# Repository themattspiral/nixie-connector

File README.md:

#nixie-connector

EAGLE schematic and board layout for my Nixie tube connector board for the ArduiNIX shield.

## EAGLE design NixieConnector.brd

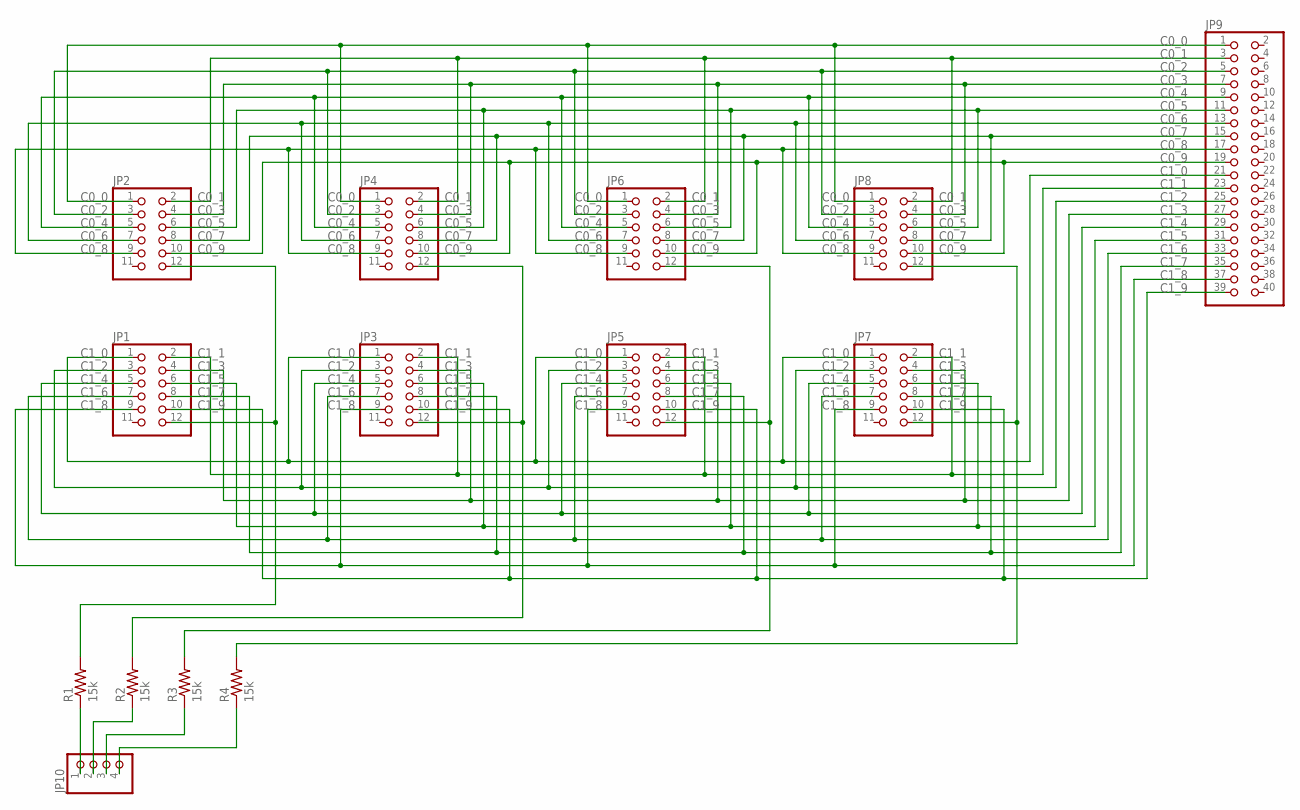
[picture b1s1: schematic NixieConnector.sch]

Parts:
JP1, JP2, JP3, JP4, JP5, JP6, JP7, JP8: PINHD-2X6; 2X06
JP9: PINHD-2X20; 2X20
JP10: PINHD-1X4; 1X04
R1, R2, R3, R4: 15k; 0204/5

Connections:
A1_IN: JP10.1, R1.1
A1_R: JP1.12, JP2.12, R1.2
A2_IN: JP10.2, R2.1
A2_R: JP3.12, JP4.12, R2.2
A3_IN: JP10.3, R3.1
A3_R: JP5.12, JP6.12, R3.2
A4_IN: JP10.4, R4.1
A4_R: JP7.12, JP8.12, R4.2
C0_0: JP2.1, JP4.1, JP6.1, JP8.1, JP9.1
C0_1: JP2.2, JP4.2, JP6.2, JP8.2, JP9.3
C0_2: JP2.3, JP4.3, JP6.3, JP8.3, JP9.5
C0_3: JP2.4, JP4.4, JP6.4, JP8.4, JP9.7
C0_4: JP2.5, JP4.5, JP6.5, JP8.5, JP9.9
C0_5: JP2.6, JP4.6, JP6.6, JP8.6, JP9.11
C0_6: JP2.7, JP4.7, JP6.7, JP8.7, JP9.13
C0_7: JP2.8, JP4.8, JP6.8, JP8.8, JP9.15
C0_8: JP2.9, JP4.9, JP6.9, JP8.9, JP9.17
C0_9: JP2.10, JP4.10, JP6.10, JP8.10, JP9.19
C1_0: JP1.1, JP3.1, JP5.1, JP7.1, JP9.21
C1_1: JP1.2, JP3.2, JP5.2, JP7.2, JP9.23
C1_2: JP1.3, JP3.3, JP5.3, JP7.3, JP9.25
C1_3: JP1.4, JP3.4, JP5.4, JP7.4, JP9.27
C1_4: JP1.5, JP3.5, JP5.5, JP7.5, JP9.29
C1_5: JP1.6, JP3.6, JP5.6, JP7.6, JP9.31
C1_6: JP1.7, JP3.7, JP5.7, JP7.7, JP9.33
C1_7: JP1.8, JP3.8, JP5.8, JP7.8, JP9.35
C1_8: JP1.9, JP3.9, JP5.9, JP7.9, JP9.37
C1_9: JP1.10, JP3.10, JP5.10, JP7.10, JP9.39

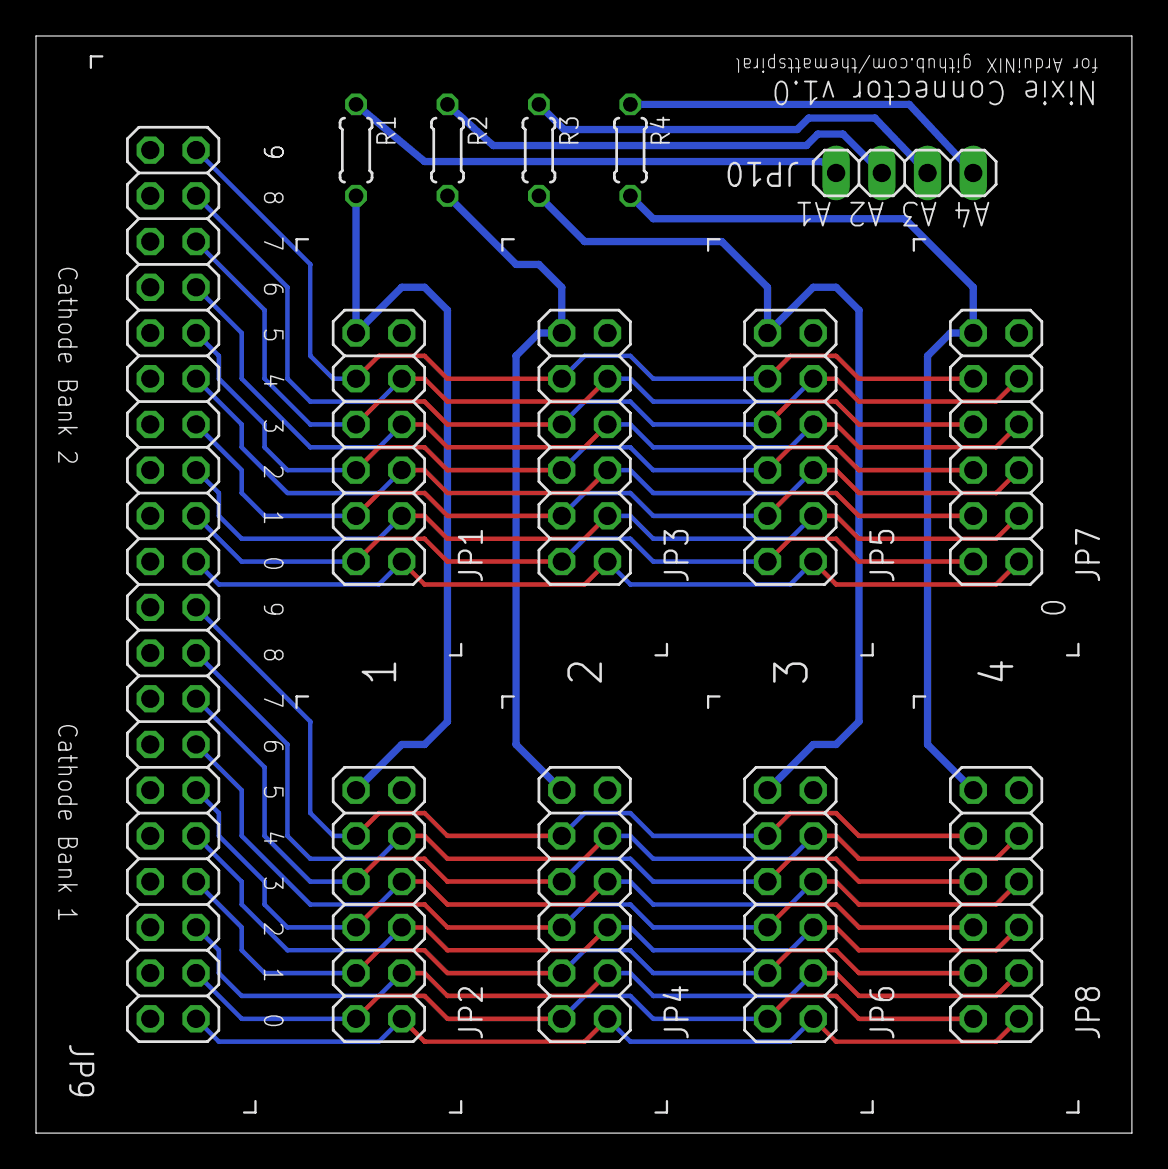
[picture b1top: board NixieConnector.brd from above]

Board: 2 copper layers, 60.9 x 61.0 mm, 14 parts (0 on the bottom side), 28 nets.

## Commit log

2015-12-05 Initial commit - Schematic and board are mostly finished
2015-12-05 Added simple readme
2015-12-05 Added MIT license file
2015-12-06 Approved ERC errors for missing values
2016-01-12 Added gerber file output
